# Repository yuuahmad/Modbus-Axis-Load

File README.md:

# arduinoModbMaster

komunikasi arduino dengan driver servo lichuan melalui rs485

part yang digunakan
- arduino nano
- modul max485
- sdcard module

yang butuh skematik ada di folder modbusBoard. software yang diginakan pakai eagle

## library
ModbusMaster https://github.com/4-20ma/ModbusMaster

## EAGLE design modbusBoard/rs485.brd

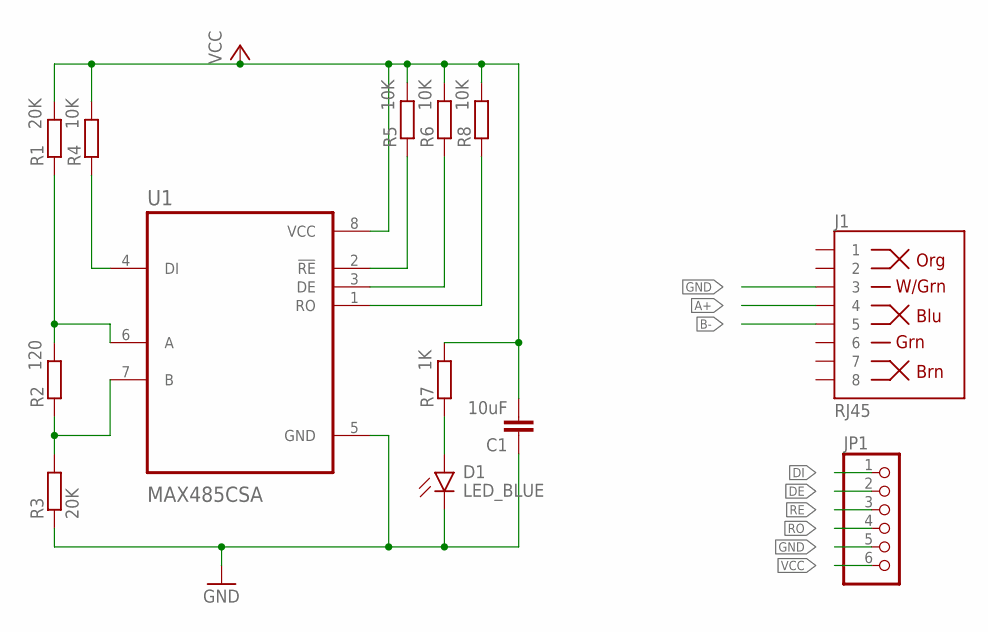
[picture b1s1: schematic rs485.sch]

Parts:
C1: 10uF; C1206
D1: LED_BLUE; LEDC3216X75N_FLAT-B
J1: RJ45; RJ45-8
JP1: PINHD-1X6; 1X06
R1, R3: 20K; M1406
R2: 120; M1406
R4, R5, R6, R8: 10K; M1406
R7: 1K; M1406
U1: MAX485CSA; SOIC127P600X175-8N

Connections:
A+: J1.4, R1.1, R2.2, U1.6 (A)
B-: J1.5, R2.1, R3.2, U1.7 (B)
DE: JP1.2, R6.1, U1.3 (DE)
DI: JP1.1, R4.1, U1.4 (DI)
GND: C1.1, D1.C, J1.3, JP1.5, R3.1, U1.5 (GND)
unnamed: D1.A, R7.1
RE: JP1.3, R5.1, U1.2 (!RE)
RO: JP1.4, R8.1, U1.1 (RO)
VCC: C1.2, JP1.6, R1.2, R4.2, R5.2, R6.2, R7.2, R8.2, U1.8 (VCC)

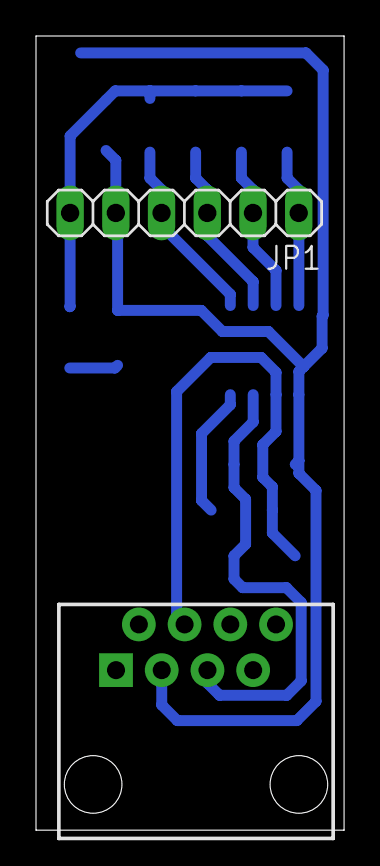
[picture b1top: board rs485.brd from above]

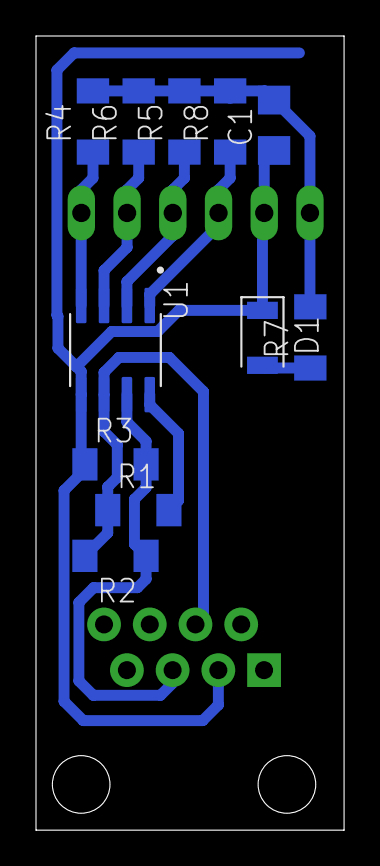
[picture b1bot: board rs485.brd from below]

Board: 2 copper layers, 17.1 x 44.1 mm, 13 parts (11 on the bottom side), 9 nets.

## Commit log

2023-12-22 tes fungsi rtc, sd, dan tulis data sederhana csv
2023-12-22 sejauh ini
2023-12-23 modbus, rtc, lcd work tanpa komputer
2023-12-23 jam 6 sore
2023-12-24 work!!!!! fitur aktif rtc,sd,modbus
2023-12-24 merapikan kode dan buat folder work
2023-12-24 percepat upload msd, perbaiki testing

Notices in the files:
parts and their libraries:
SparkFun-Connectors: Licensing: Creative Commons ShareAlike 4.0 International - https://creativecommons.org/licenses/by-sa/4.0
